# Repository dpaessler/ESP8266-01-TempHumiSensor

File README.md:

# ESP8266-01 temperature and humidity sensor

I use some of these with USB power adapters to measure temperature and humidity with a DHT22/AM2302. Optionally you can add a DS18B20 for more precise temperature readings.

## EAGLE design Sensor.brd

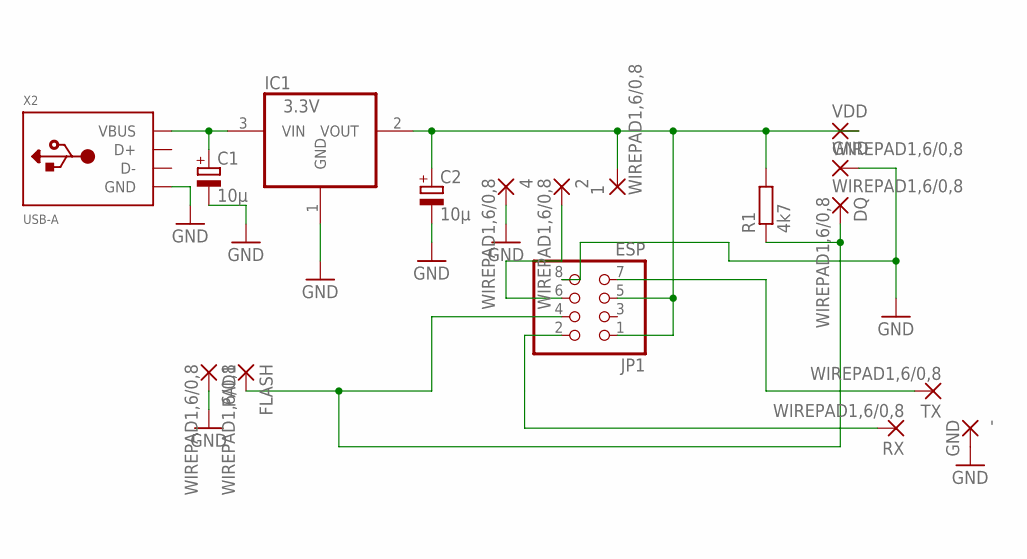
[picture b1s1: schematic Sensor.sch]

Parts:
1, 2, 4: WIREPAD1,6/0,8; 1,6/0,8
-: GND; 1,6/0,8
C1, C2: 10µ; A/3216-18W
DQ: WIREPAD1,6/0,8; 1,6/0,8
FLASH: WIREPAD1,6/0,8; 1,6/0,8
GND: WIREPAD1,6/0,8; 1,6/0,8
IC1: 3.3V; SOT223
JP1: ESP; 2X04
PAD1: WIREPAD1,6/0,8; 1,6/0,8
R1: 4k7; R1206
RX: WIREPAD1,6/0,8; 1,6/0,8
TX: WIREPAD1,6/0,8; 1,6/0,8
VDD: WIREPAD1,6/0,8; 1,6/0,8
X2: USB-A; MOLEX_480371000

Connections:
3V3: 1.1, C2.+, IC1.2 (VOUT), JP1.1, JP1.5, R1.2, VDD.1
GND: 4.1, -.1, C1.-, C2.-, GND.1, IC1.1 (GND), JP1.8, PAD1.1, X2.4 (GND)
GPIO0: DQ.1, FLASH.1, JP1.4, R1.1
GPIO2: 2.1, JP1.6
RX: JP1.2, RX.1
TX: JP1.7, TX.1
VBUS: C1.+, IC1.3 (VIN), X2.1 (VBUS)

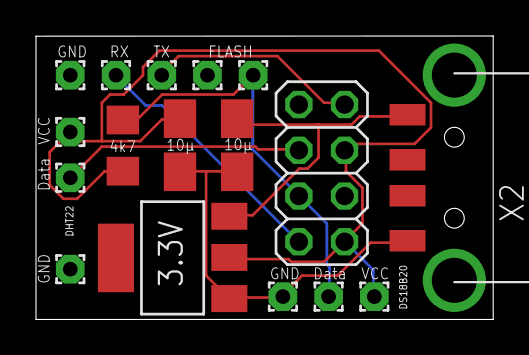
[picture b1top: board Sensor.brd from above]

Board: 2 copper layers, 25.4 x 15.7 mm, 17 parts (0 on the bottom side), 7 nets.

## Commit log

2017-07-02 some cosmetic changes
